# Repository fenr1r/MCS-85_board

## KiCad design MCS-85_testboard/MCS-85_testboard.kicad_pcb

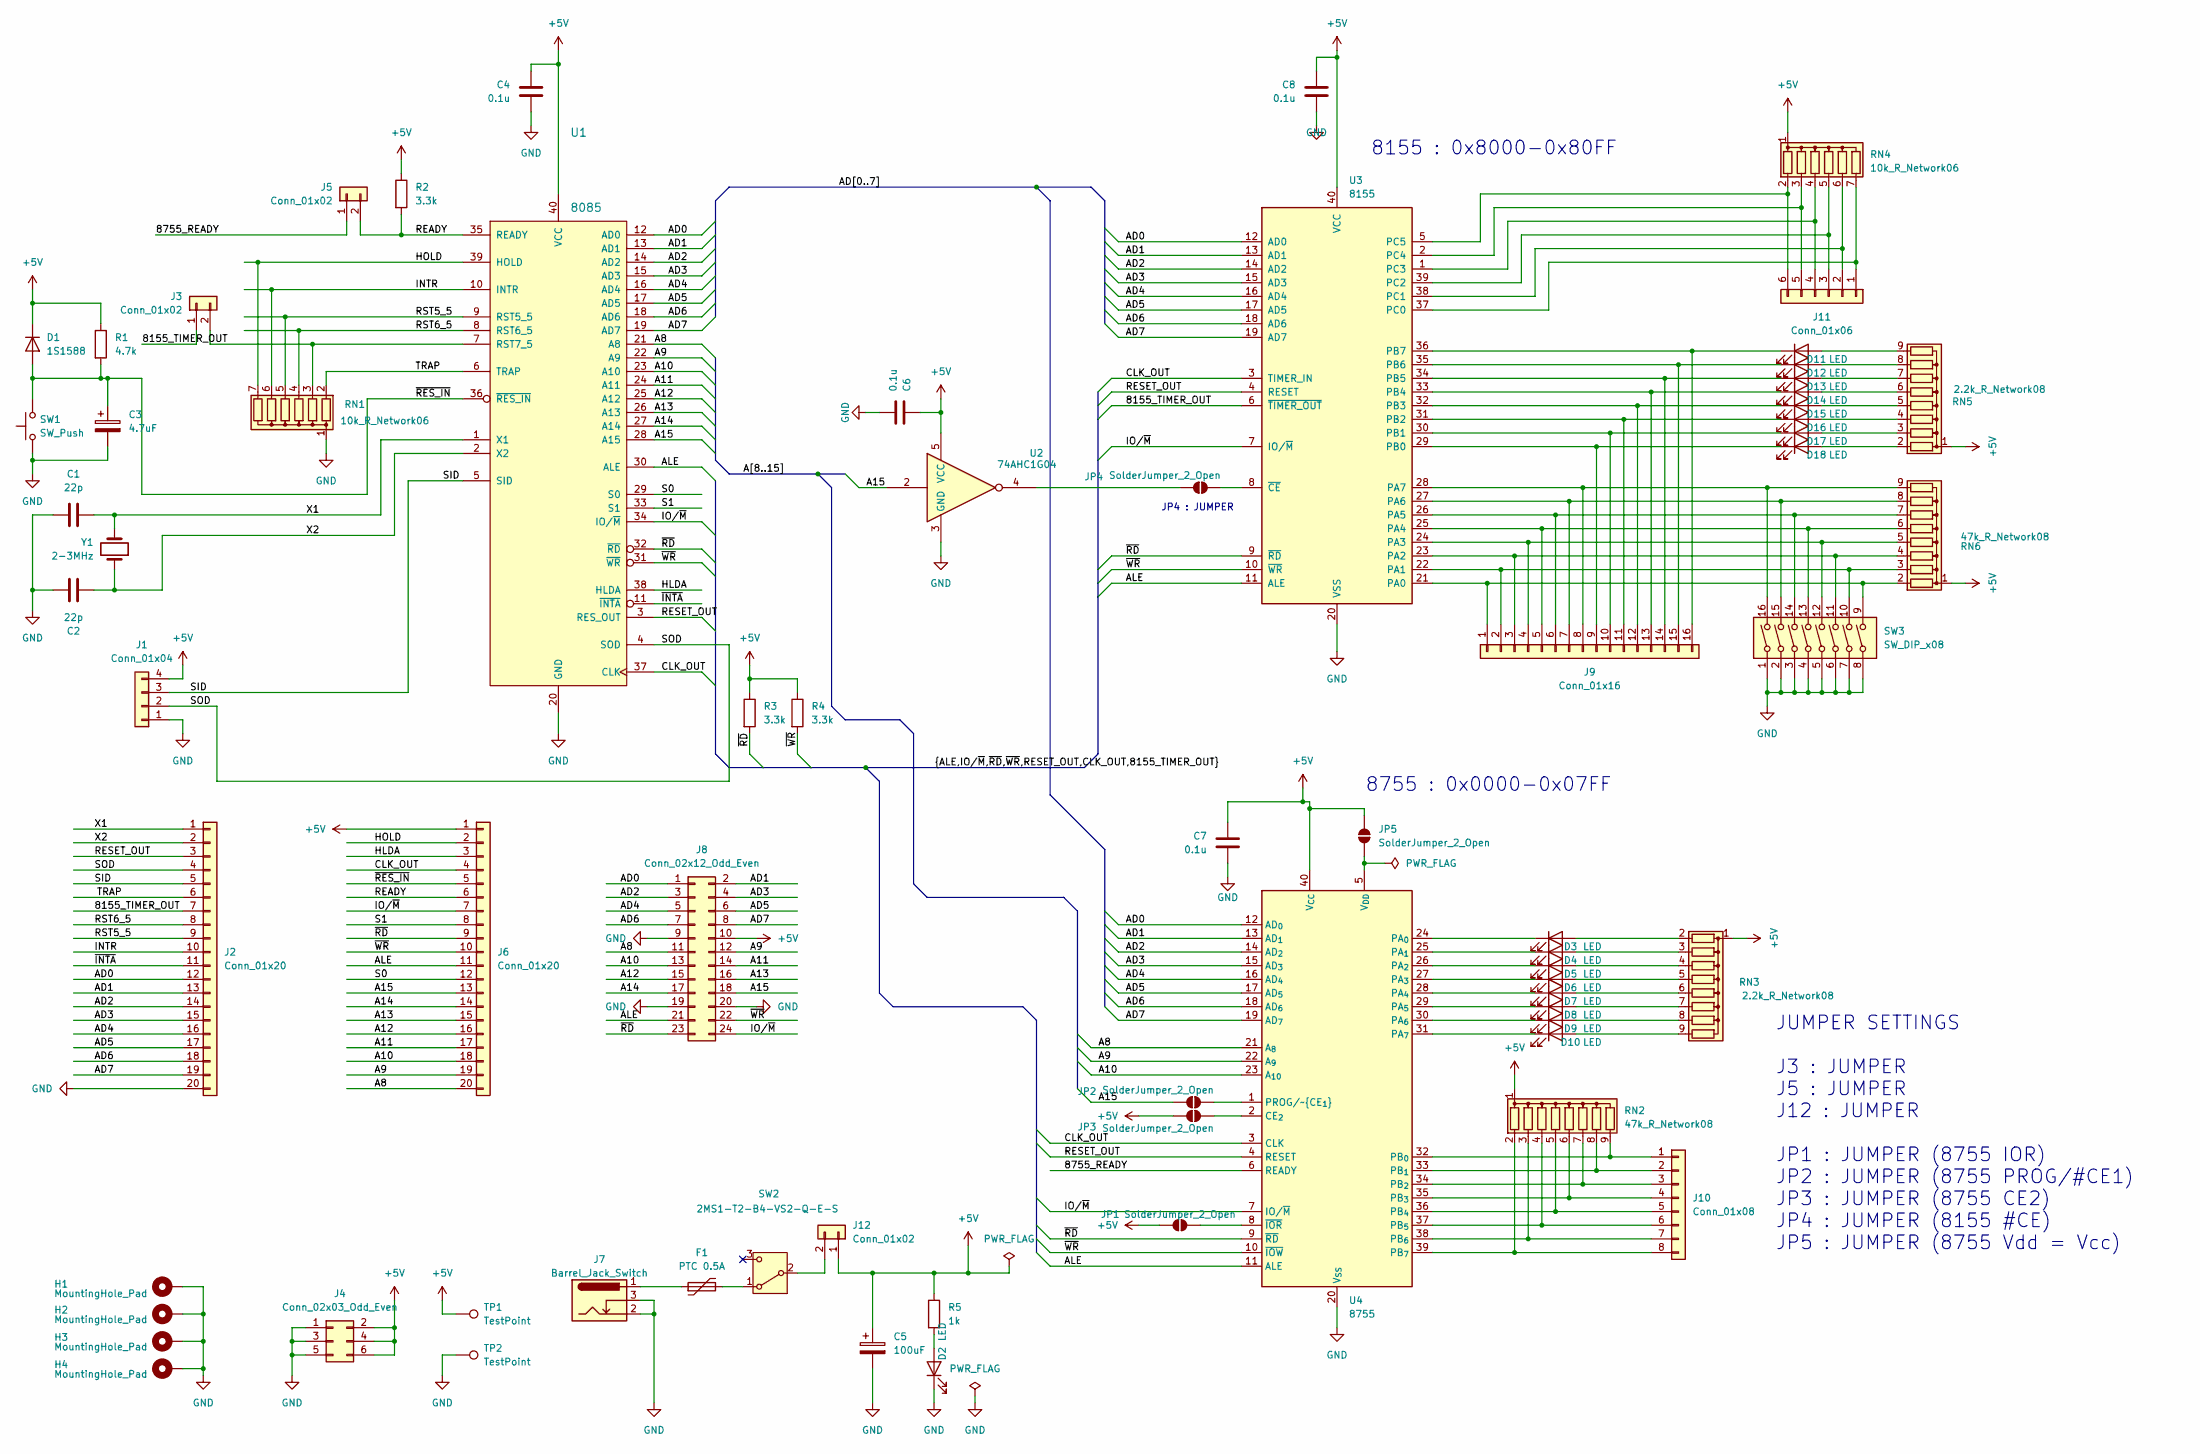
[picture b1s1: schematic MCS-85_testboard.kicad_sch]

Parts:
C1, C2: 22p; C_Disc_D4.7mm_W2.5mm_P5.00mm
C3: 4.7uF; CP_Radial_D5.0mm_P2.00mm
C4, C6, C7, C8: 0.1u; C_Disc_D4.7mm_W2.5mm_P5.00mm
C5: 100uF; CP_Radial_D8.0mm_P5.00mm
D1: 1S1588; D_DO-35_SOD27_P7.62mm_Horizontal
D2: LED; LED_0805_2012Metric_Pad1.15x1.40mm_HandSolder
D3, D4, D5, D6, D7, D8, D9, D10, D11, D12, D13, D14, D15, D16, D17, D18: LED; LED_D5.0mm
F1: PTC 0.5A; Fuse_1812_4532Metric_Pad1.30x3.40mm_HandSolder
H1, H2, H3, H4: MountingHole_Pad; MountingHole_3.2mm_M3_Pad
J1: Conn_01x04; PinHeader_1x04_P2.54mm_Vertical
J2, J6: Conn_01x20; PinHeader_1x20_P2.54mm_Vertical
J3, J5, J12: Conn_01x02; PinHeader_1x02_P2.54mm_Vertical
J4: Conn_02x03_Odd_Even; PinHeader_2x03_P2.54mm_Vertical
J7: Barrel_Jack_Switch; BarrelJack_Horizontal
J8: Conn_02x12_Odd_Even; PinHeader_2x12_P2.54mm_Vertical
J9: Conn_01x16; PinHeader_1x16_P2.54mm_Vertical
J10: Conn_01x08; PinHeader_1x08_P2.54mm_Vertical
J11: Conn_01x06; PinHeader_1x06_P2.54mm_Vertical
JP1, JP2, JP3, JP4, JP5: SolderJumper_2_Open; SolderJumper-2_P1.3mm_Open_Pad1.0x1.5mm
R1: 4.7k; R_Axial_DIN0207_L6.3mm_D2.5mm_P7.62mm_Horizontal
R2, R3, R4: 3.3k; R_Axial_DIN0207_L6.3mm_D2.5mm_P7.62mm_Horizontal
R5: 1k; R_Axial_DIN0207_L6.3mm_D2.5mm_P7.62mm_Horizontal
RN1, RN4: 10k_R_Network06; R_Array_SIP7
RN2, RN6: 47k_R_Network08; R_Array_SIP9
RN3, RN5: 2.2k_R_Network08; R_Array_SIP9
SW1: SW_Push; SW_PUSH_6mm
SW2: 2MS1-T2-B4-VS2-Q-E-S; SW_Slide_SPDT_Straight_CK_OS102011MS2Q
SW3: SW_DIP_x08; SW_DIP_SPSTx08_Slide_9.78x22.5mm_W7.62mm_P2.54mm
TP1, TP2: TestPoint; PinHeader_1x01_P2.54mm_Vertical
U1: 8085; DIP-40_W15.24mm
U2: 74AHC1G04; SOT-23-5_HandSoldering
U3: 8155; DIP-40_W15.24mm
U4: 8755; DIP_Socket-40_W11.9mm_W12.7mm_W15.24mm_W17.78mm_W18.5mm_3M_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
Y1: 2-3MHz; Crystal_HC49-U_Vertical

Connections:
+5V: C4.1, C5.1, C6.1, C7.1, C8.1, D1.1 (K), J1.4, J4.2, J4.4, J4.6, J6.1, J8.10, J12.1, JP1.2 (B), JP3.2 (B), JP5.2 (B), R1.1, R2.1, R3.1, R4.1, R5.1, RN2.1 (common), RN3.1 (common), RN4.1 (common), RN5.1 (common), RN6.1 (common), TP1.1, U1.40 (VCC), U2.5 (VCC), U3.40 (VCC), U4.40 (V_{CC})
/8155_TIMER_OUT: J2.7, J3.1, U3.6 (~TIMER_OUT)
/8755_READY: J5.1, U4.6 (READY)
/A8: J6.20, J8.11, U1.21 (A8), U4.21 (A_{8})
/A9: J6.19, J8.12, U1.22 (A9), U4.22 (A_{9})
/A10: J6.18, J8.13, U1.23 (A10), U4.23 (A_{10})
/A11: J6.17, J8.14, U1.24 (A11)
/A12: J6.16, J8.15, U1.25 (A12)
/A13: J6.15, J8.16, U1.26 (A13)
/A14: J6.14, J8.17, U1.27 (A14)
/A15: J6.13, J8.18, JP2.2 (B), U1.28 (A15), U2.2
/AD0: J2.12, J8.1, U1.12 (AD0), U3.12 (AD0), U4.12 (AD_{0})
/AD1: J2.13, J8.2, U1.13 (AD1), U3.13 (AD1), U4.13 (AD_{1})
/AD2: J2.14, J8.3, U1.14 (AD2), U3.14 (AD2), U4.14 (AD_{2})
/AD3: J2.15, J8.4, U1.15 (AD3), U3.15 (AD3), U4.15 (AD_{3})
/AD4: J2.16, J8.5, U1.16 (AD4), U3.16 (AD4), U4.16 (AD_{4})
/AD5: J2.17, J8.6, U1.17 (AD5), U3.17 (AD5), U4.17 (AD_{5})
/AD6: J2.18, J8.7, U1.18 (AD6), U3.18 (AD6), U4.18 (AD_{6})
/AD7: J2.19, J8.8, U1.19 (AD7), U3.19 (AD7), U4.19 (AD_{7})
/ALE: J6.11, J8.21, U1.30 (ALE), U3.11 (ALE), U4.11 (ALE)
/CLK_OUT: J6.4, U1.37 (CLK), U3.3 (TIMER_IN), U4.3 (CLK)
/HLDA: J6.3, U1.38 (HLDA)
/HOLD: J6.2, RN1.7 (R6), U1.39 (HOLD)
/INTR: J2.10, RN1.6 (R5), U1.10 (INTR)
/IO/~M: J6.7, J8.24, U1.34 (IO/~M), U3.7 (IO/~M), U4.7 (IO/~M)
/READY: J5.2, J6.6, R2.2, U1.35 (READY)
/RESET_OUT: J2.3, U1.3 (RES_OUT), U3.4 (RESET), U4.4 (RESET)
/RST5_5: J2.9, RN1.5 (R4), U1.9 (RST5_5)
/RST6_5: J2.8, RN1.4 (R3), U1.8 (RST6_5)
/S0: J6.12, U1.29 (S0)
/S1: J6.8, U1.33 (S1)
/SID: J1.3, J2.5, U1.5 (SID)
/SOD: J1.2, J2.4, U1.4 (SOD)
/TRAP: J2.6, RN1.2 (R1), U1.6 (TRAP)
/X1: C1.2, J2.1, U1.1 (X1), Y1.2
/X2: C2.2, J2.2, U1.2 (X2), Y1.1
/~INTA: J2.11, U1.11 (~INTA)
/~RD: J6.9, J8.23, R3.2, U1.32 (~RD), U3.9 (~RD), U4.9 (~RD)
/~RES_IN: C3.1, D1.2 (A), J6.5, R1.2, SW1.2, U1.36 (~RES_IN)
/~WR: J6.10, J8.22, R4.2, U1.31 (~WR), U3.10 (~WR), U4.10 (~IOW)
GND: C1.1, C2.1, C3.2, C4.2, C5.2, C6.2, C7.2, C8.2, D2.1 (K), H1.1, H2.1, H3.1, H4.1, J1.1, J2.20, J4.1, J4.3, J4.5, J7.2, J7.3, J8.9, J8.19, J8.20, RN1.1 (common), SW1.1, SW3.1, SW3.2, SW3.3, SW3.4, SW3.5, SW3.6, SW3.7, SW3.8, TP2.1, U1.20 (GND), U2.3 (GND), U3.20 (VSS), U4.20 (V_{SS})
unnamed: D2.2 (A), R5.2
unnamed: D3.2 (A), RN3.2 (R1)
unnamed: D3.1 (K), U4.24 (PA_{0})
unnamed: D4.2 (A), RN3.3 (R2)
unnamed: D4.1 (K), U4.25 (PA_{1})
unnamed: D5.2 (A), RN3.4 (R3)
unnamed: D5.1 (K), U4.26 (PA_{2})
unnamed: D6.2 (A), RN3.5 (R4)
unnamed: D6.1 (K), U4.27 (PA_{3})
unnamed: D7.2 (A), RN3.6 (R5)
unnamed: D7.1 (K), U4.28 (PA_{4})
unnamed: D8.2 (A), RN3.7 (R6)
unnamed: D8.1 (K), U4.29 (PA_{5})
unnamed: D9.2 (A), RN3.8 (R7)
unnamed: D9.1 (K), U4.30 (PA_{6})
unnamed: D10.2 (A), RN3.9 (R8)
unnamed: D10.1 (K), U4.31 (PA_{7})
unnamed: D11.2 (A), RN5.9 (R8)
unnamed: D11.1 (K), J9.16, U3.36 (PB7)
unnamed: D12.2 (A), RN5.8 (R7)
unnamed: D12.1 (K), J9.15, U3.35 (PB6)
unnamed: D13.2 (A), RN5.7 (R6)
unnamed: D13.1 (K), J9.14, U3.34 (PB5)
unnamed: D14.2 (A), RN5.6 (R5)
unnamed: D14.1 (K), J9.13, U3.33 (PB4)
unnamed: D15.2 (A), RN5.5 (R4)
unnamed: D15.1 (K), J9.12, U3.32 (PB3)
unnamed: D16.2 (A), RN5.4 (R3)
unnamed: D16.1 (K), J9.11, U3.31 (PB2)
unnamed: D17.2 (A), RN5.3 (R2)
unnamed: D17.1 (K), J9.10, U3.30 (PB1)
unnamed: D18.2 (A), RN5.2 (R1)
unnamed: D18.1 (K), J9.9, U3.29 (PB0)
unnamed: F1.1, J7.1
unnamed: J3.2, RN1.3 (R2), U1.7 (RST7_5)
unnamed: J9.1, RN6.2 (R1), SW3.9, U3.21 (PA0)
unnamed: J9.2, RN6.3 (R2), SW3.10, U3.22 (PA1)
unnamed: J9.3, RN6.4 (R3), SW3.11, U3.23 (PA2)
unnamed: J9.4, RN6.5 (R4), SW3.12, U3.24 (PA3)
unnamed: J9.5, RN6.6 (R5), SW3.13, U3.25 (PA4)
unnamed: J9.6, RN6.7 (R6), SW3.14, U3.26 (PA5)
unnamed: J9.7, RN6.8 (R7), SW3.15, U3.27 (PA6)
unnamed: J9.8, RN6.9 (R8), SW3.16, U3.28 (PA7)
unnamed: J10.1, RN2.9 (R8), U4.32 (PB_{0})
unnamed: J10.2, RN2.8 (R7), U4.33 (PB_{1})
unnamed: J10.3, RN2.7 (R6), U4.34 (PB_{2})
unnamed: J10.4, RN2.6 (R5), U4.35 (PB_{3})
unnamed: J10.5, RN2.5 (R4), U4.36 (PB_{4})
unnamed: J10.6, RN2.4 (R3), U4.37 (PB_{5})
unnamed: J10.7, RN2.3 (R2), U4.38 (PB_{6})
unnamed: J10.8, RN2.2 (R1), U4.39 (PB_{7})
unnamed: J11.1, RN4.7 (R6), U3.37 (PC0)
unnamed: J11.2, RN4.6 (R5), U3.38 (PC1)
unnamed: J11.3, RN4.5 (R4), U3.39 (PC2)
unnamed: J11.4, RN4.4 (R3), U3.1 (PC3)
unnamed: J11.5, RN4.3 (R2), U3.2 (PC4)
unnamed: J11.6, RN4.2 (R1), U3.5 (PC5)
unnamed: J12.2, SW2.2 (B)
unnamed: JP1.1 (A), U4.8 (~IOR)
unnamed: JP2.1 (A), U4.1 (PROG/~CE_{1})
unnamed: JP3.1 (A), U4.2 (CE_{2})
unnamed: JP4.1 (A), U3.8 (~CE)
unnamed: JP4.2 (B), U2.4
unnamed: JP5.1 (A), U4.5 (V_{DD})
unnamed: F1.2, SW2.1 (A)

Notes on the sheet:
JUMPER SETTINGS J3 : JUMPER J5 : JUMPER J12 : JUMPER JP1 : JUMPER (8755 IOR) JP2 : JUMPER (8755 PROG/#CE1) JP3 : JUMPER (8755 CE2) JP4 : JUMPER (8155 #CE) JP5 : JUMPER (8755 Vdd = Vcc)
8755 : 0x0000-0x07FF
JP4 : JUMPER
8155 : 0x8000-0x80FF

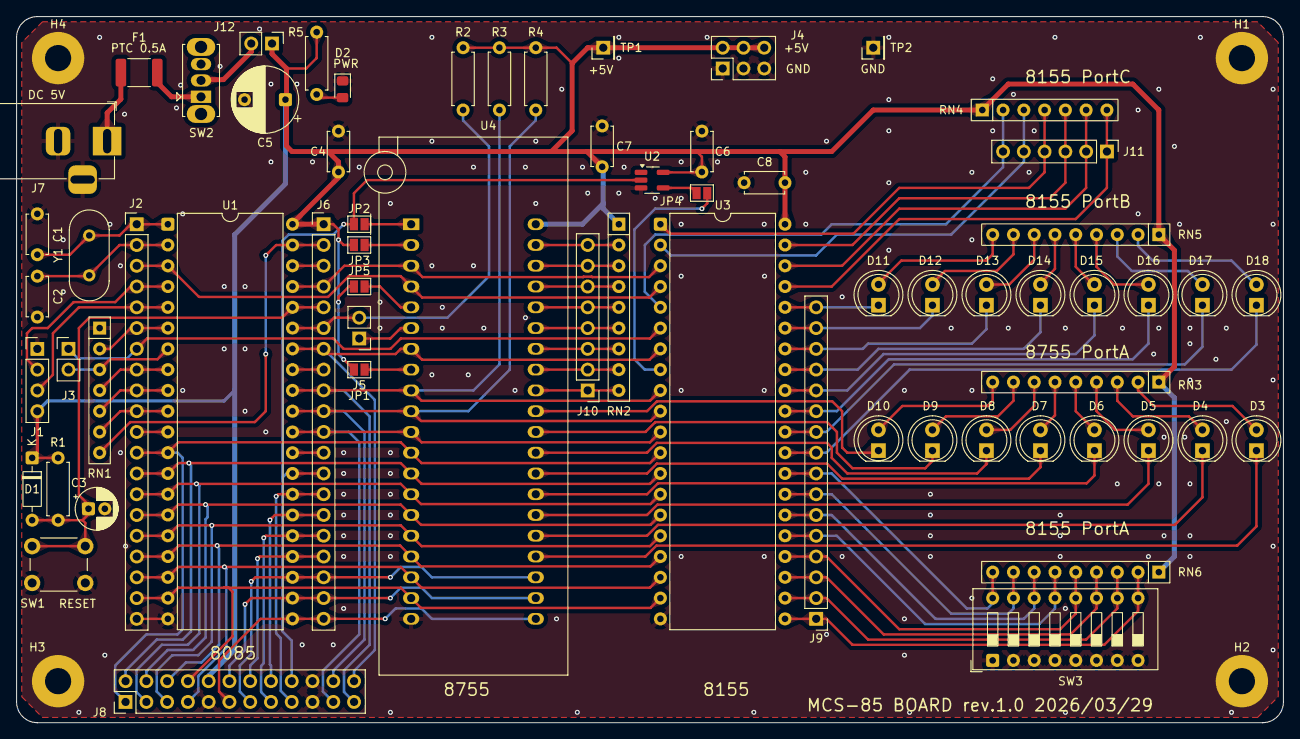
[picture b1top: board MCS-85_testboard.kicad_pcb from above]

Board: 2 copper layers, 154.9 x 86.4 mm, 69 parts (0 on the bottom side), 106 nets.

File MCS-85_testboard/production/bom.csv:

Designator,Footprint,Quantity,Value,LCSC Part #
"C1, C2",C_Disc_D4.7mm_W2.5mm_P5.00mm,2,22p,
C3,CP_Radial_D5.0mm_P2.00mm,1,4.7uF,
"C4, C6, C7, C8",C_Disc_D4.7mm_W2.5mm_P5.00mm,4,0.1u,
C5,CP_Radial_D8.0mm_P5.00mm,1,100uF,
D1,D_DO-35_SOD27_P7.62mm_Horizontal,1,1S1588,
"D10, D11, D12, D13, D14, D15, D16, D17, D18, D3, D4, D5, D6, D7, D8, D9",LED_D5.0mm,16,LED,
D2,0805,1,LED,
F1,1812,1,PTC 0.5A,
J1,PinHeader_1x04_P2.54mm_Vertical,1,Conn_01x04,
J10,PinHeader_1x08_P2.54mm_Vertical,1,Conn_01x08,
J11,PinHeader_1x06_P2.54mm_Vertical,1,Conn_01x06,
"J12, J3, J5",PinHeader_1x02_P2.54mm_Vertical,3,Conn_01x02,
"J2, J6",PinHeader_1x20_P2.54mm_Vertical,2,Conn_01x20,
J4,PinHeader_2x03_P2.54mm_Vertical,1,Conn_02x03_Odd_Even,
J7,BarrelJack_Horizontal,1,Barrel_Jack_Switch,
J8,PinHeader_2x12_P2.54mm_Vertical,1,Conn_02x12_Odd_Even,
J9,PinHeader_1x16_P2.54mm_Vertical,1,Conn_01x16,
R1,R_Axial_DIN0207_L6.3mm_D2.5mm_P7.62mm_Horizontal,1,4.7k,
"R2, R3, R4",R_Axial_DIN0207_L6.3mm_D2.5mm_P7.62mm_Horizontal,3,3.3k,
R5,R_Axial_DIN0207_L6.3mm_D2.5mm_P7.62mm_Horizontal,1,1k,
"RN1, RN4",R_Array_SIP7,2,10k_R_Network06,
"RN2, RN6",R_Array_SIP9,2,47k_R_Network08,
"RN3, RN5",R_Array_SIP9,2,2.2k_R_Network08,
SW1,SW_PUSH_6mm,1,SW_Push,
SW2,SW_Slide_SPDT_Straight_CK_OS102011MS2Q,1,2MS1-T2-B4-VS2-Q-E-S,
SW3,SW_DIP_SPSTx08_Slide_9.78x22.5mm_W7.62mm_P2.54mm,1,SW_DIP_x08,
"TP1, TP2",PinHeader_1x01_P2.54mm_Vertical,2,TestPoint,
U1,DIP-40_W15.24mm,1,8085,
U2,SOT-23-5_HandSoldering,1,74AHC1G04,
U3,DIP-40_W15.24mm,1,8155,
U4,DIP_Socket-40_W11.9mm_W12.7mm_W15.24mm_W17.78mm_W18.5mm_3M_240-1280-00-0602J,1,8755,
Y1,Crystal_HC49-U_Vertical,1,2-3MHz,
